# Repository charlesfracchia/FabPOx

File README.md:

FabPOx
======

Open Source DIY Pulse Oximeter with Bluetooth

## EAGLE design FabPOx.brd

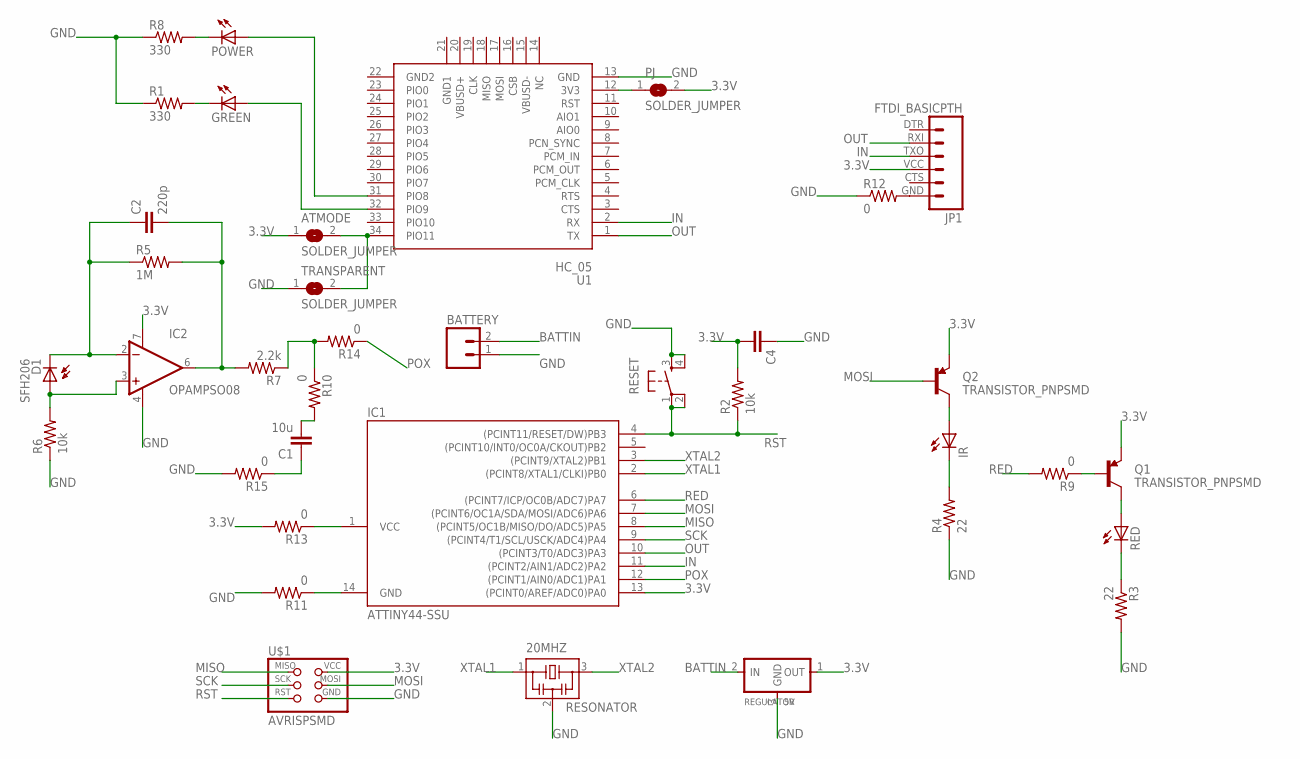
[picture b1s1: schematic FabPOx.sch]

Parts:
20MHZ: RESONATOR; EFOBM
ATMODE: SOLDER_JUMPER; SJFAB
BATTERY: M02PTH; 1X02
C1: 10u; 1206
C2: 220p; 1206
C4: CAP1206; 1206
D1: SFH206
GREEN: LED1206; 1206
IC1: ATTINY44-SSU; SOIC14
IC2: OPAMPSO08; SO08
IR: LED3MM
JP1: FTDI_BASICPTH; FTDI_BASIC
PJ: SOLDER_JUMPER; SJFAB
POWER: LED1206; 1206
Q1, Q2: TRANSISTOR_PNPSMD; SOT23-3
R1, R8: 330; R1206
R2, R6: 10k; R1206
R3, R4: 22; R1206
R5: 1M; R1206
R7: 2.2k; R1206
R9, R10, R11, R12, R13, R14, R15: 0; R1206
RED: LED3MM
REGULATOR: 5V; SOT23
RESET: 6MM_SWITCH6MM_SWITCH; 6MM_SWITCH
TRANSPARENT: SOLDER_JUMPER; SJFAB
U1: HC_05; BLUETOOTH_SMD
U$1: AVRISPSMD; 2X03SMD

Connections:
3.3V: ATMODE.1, C4.2, IC1.13 ((PCINT0/AREF/ADC0)PA0), IC2.7 (V+), JP1.VCC (4), PJ.2, Q1.2 (E), Q2.2 (E), R2.2, R13.2, REGULATOR.1 (OUT), U$1.2 (VCC)
BATTIN: BATTERY.2, REGULATOR.2 (IN)
GND: 20MHZ.2, BATTERY.1, C4.1, IC2.4 (V-), IR.K (C), R1.1, R3.1, R3.2, R4.1, R4.2, R6.1, R8.1, R11.2, R12.1, R15.2, RED.K (C), REGULATOR.3 (GND), RESET.3 (S), RESET.4 (S1), TRANSPARENT.1, U1.13 (GND), U$1.6 (GND)
IN: IC1.11 ((PCINT2/AIN1/ADC2)PA2), JP1.TXO (3), U1.2 (RX)
MISO: IC1.8 ((PCINT5/OC1B/MISO/DO/ADC5)PA5), U$1.1 (MISO)
MOSI: IC1.7 ((PCINT6/OC1A/SDA/MOSI/ADC6)PA6), Q2.1 (B), U$1.4 (MOSI)
unnamed: Q1.1 (B), R9.1
unnamed: IR.A, Q2.3 (C)
unnamed: Q1.3 (C), RED.A
unnamed: R7.1, R10.1, R14.2
unnamed: IC1.14 (GND), R11.1
unnamed: JP1.GND (6), R12.2
unnamed: C2.2, IC2.6 (OUT), R5.2, R7.2
unnamed: C2.1, D1.K (C), IC2.2 (-IN), R5.1
unnamed: IC1.1 (VCC), R13.1
unnamed: D1.A, IC2.3 (+IN), R6.2
unnamed: PJ.1, U1.12 (3V3)
unnamed: C1.2, R10.2
unnamed: C1.1, R15.1
unnamed: ATMODE.2, TRANSPARENT.2, U1.34 (PIO11)
unnamed: GREEN.2 (C), R1.2
unnamed: POWER.2 (C), R8.2
unnamed: POWER.1 (A), U1.31 (PIO8)
unnamed: GREEN.1 (A), U1.32 (PIO9)
OUT: IC1.10 ((PCINT3/T0/ADC3)PA3), JP1.RXI (2), U1.1 (TX)
POX: IC1.12 ((PCINT1/AIN0/ADC1)PA1), R14.1
RED: IC1.6 ((PCINT7/ICP/OC0B/ADC7)PA7), R9.2
RST: IC1.4 ((PCINT11/RESET/DW)PB3), R2.1, RESET.1, RESET.2 (P1), U$1.5 (RST)
SCK: IC1.9 ((PCINT4/T1/SCL/USCK/ADC4)PA4), U$1.3 (SCK)
XTAL1: 20MHZ.1, IC1.2 ((PCINT8/XTAL1/CLKI)PB0)
XTAL2: 20MHZ.3, IC1.3 ((PCINT9/XTAL2)PB1)

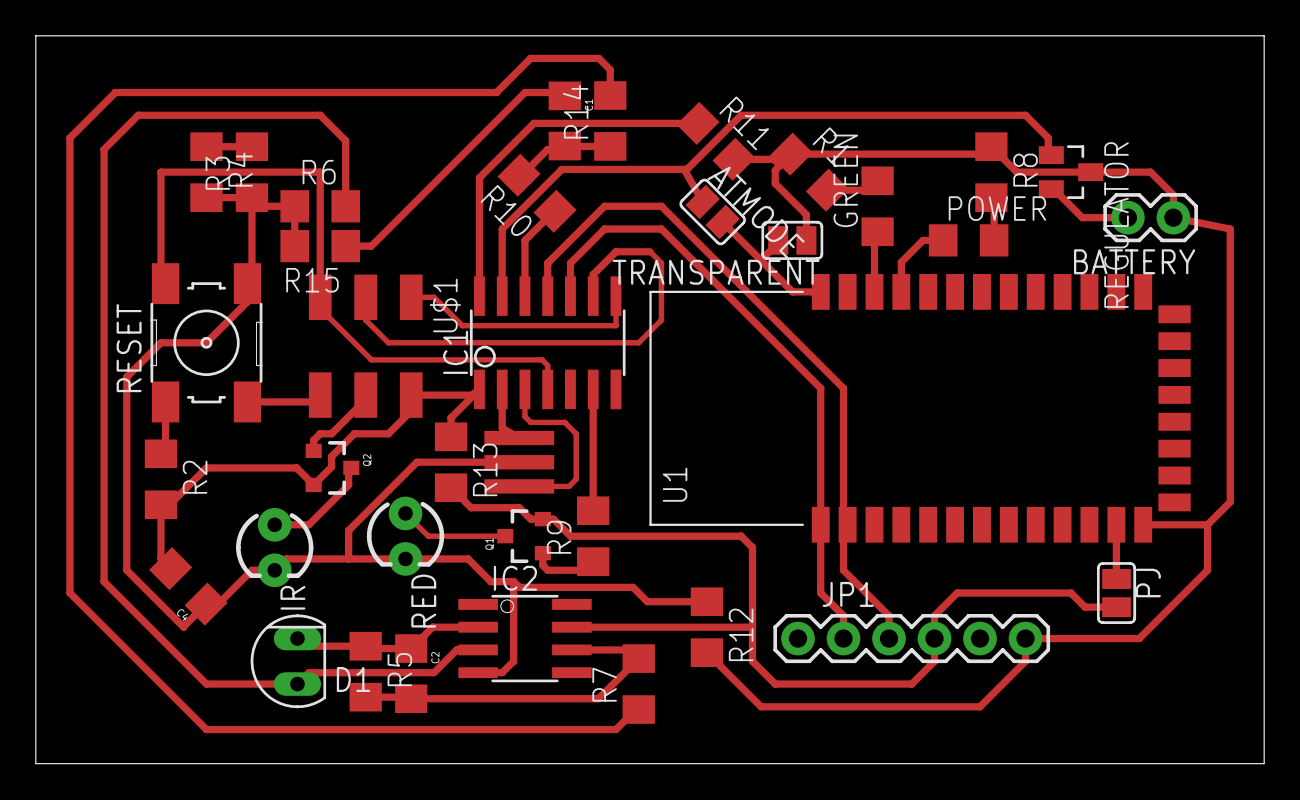
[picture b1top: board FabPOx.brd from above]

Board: 2 copper layers, 68.6 x 40.6 mm, 37 parts (0 on the bottom side), 31 nets.

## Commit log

2013-09-30 v1 added, bluetooth, design from class
    Pulse Ox Design derived from clas with added HC4/05/06 based bluetooth
    communication and assorted AT / Transparent mode solder jumper
    selectors. Using ATTiny44.
    Have not tested the board yet. Mostly 16mil traces with a couple of
    12mil ones.
2013-10-02 Added EAGLE temp files to Git Ignore
2013-10-02 Added correct syntax for ignoring temp EAGLE board and schematic
2013-10-02 Fixed value on capacitor C1

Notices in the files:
parts and their libraries:
SparkFun-Connectors: Licensing: CC v3.0 Share-Alike You are welcome to use this library for commercial purposes.
